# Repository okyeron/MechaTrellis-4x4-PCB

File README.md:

## MechaTrellis RGB Driver PCB for 4x4 Keypad PCB

PCB files for the MechaTrellis 4x4 keypad PCB. Format is Kicad 8.0 schematic and board layout

### Description

MechaTellis is an Adaptation/Remix of the Adafruit NeoTrellis RGB Driver PCB.  

MechaTellis was designed by Steven Noreyko/denki-oto. Original NeoTrellis design by Limor Fried/Ladyada for Adafruit Industries. 

These run the same NeoTrellis seesaw I2C chip and are fully software compatible with the NeoTrellis boards and projects.

A JST-SH 4-pin connector is included that will give you power+data access. Note JST-SH is smaller than the NeoTrellis JST-PH connector.

From the original NeoTrellis 4x4 boards:  

These 4x4 button pad boards are fully tile-able and communicate over I2C. With 5 address pins, you've got the ability to connect up to 32 together in any arrangement you like. [With our trusty seesaw I2C-to-anything chip](https://learn.adafruit.com/adafruit-seesaw-atsamd09-breakout), you don't even need to manage the NeoPixel driving. That's right! Both the button management and LED driving is completely handled for you all over plain I2C. With both Arduino/C++ and CircuitPython/Python library support, you can use these pads with any and all microcontroller or computer boards.

**You can tile up to 32 boards together by soldering them edge-to-edge and soldering closed the I2C address jumpers, then use one I2C connection for all tiled boards!**

### License

Creative Commons Attribution/Share-Alike, all text above must be included in any redistribution. See license.txt for additional details.

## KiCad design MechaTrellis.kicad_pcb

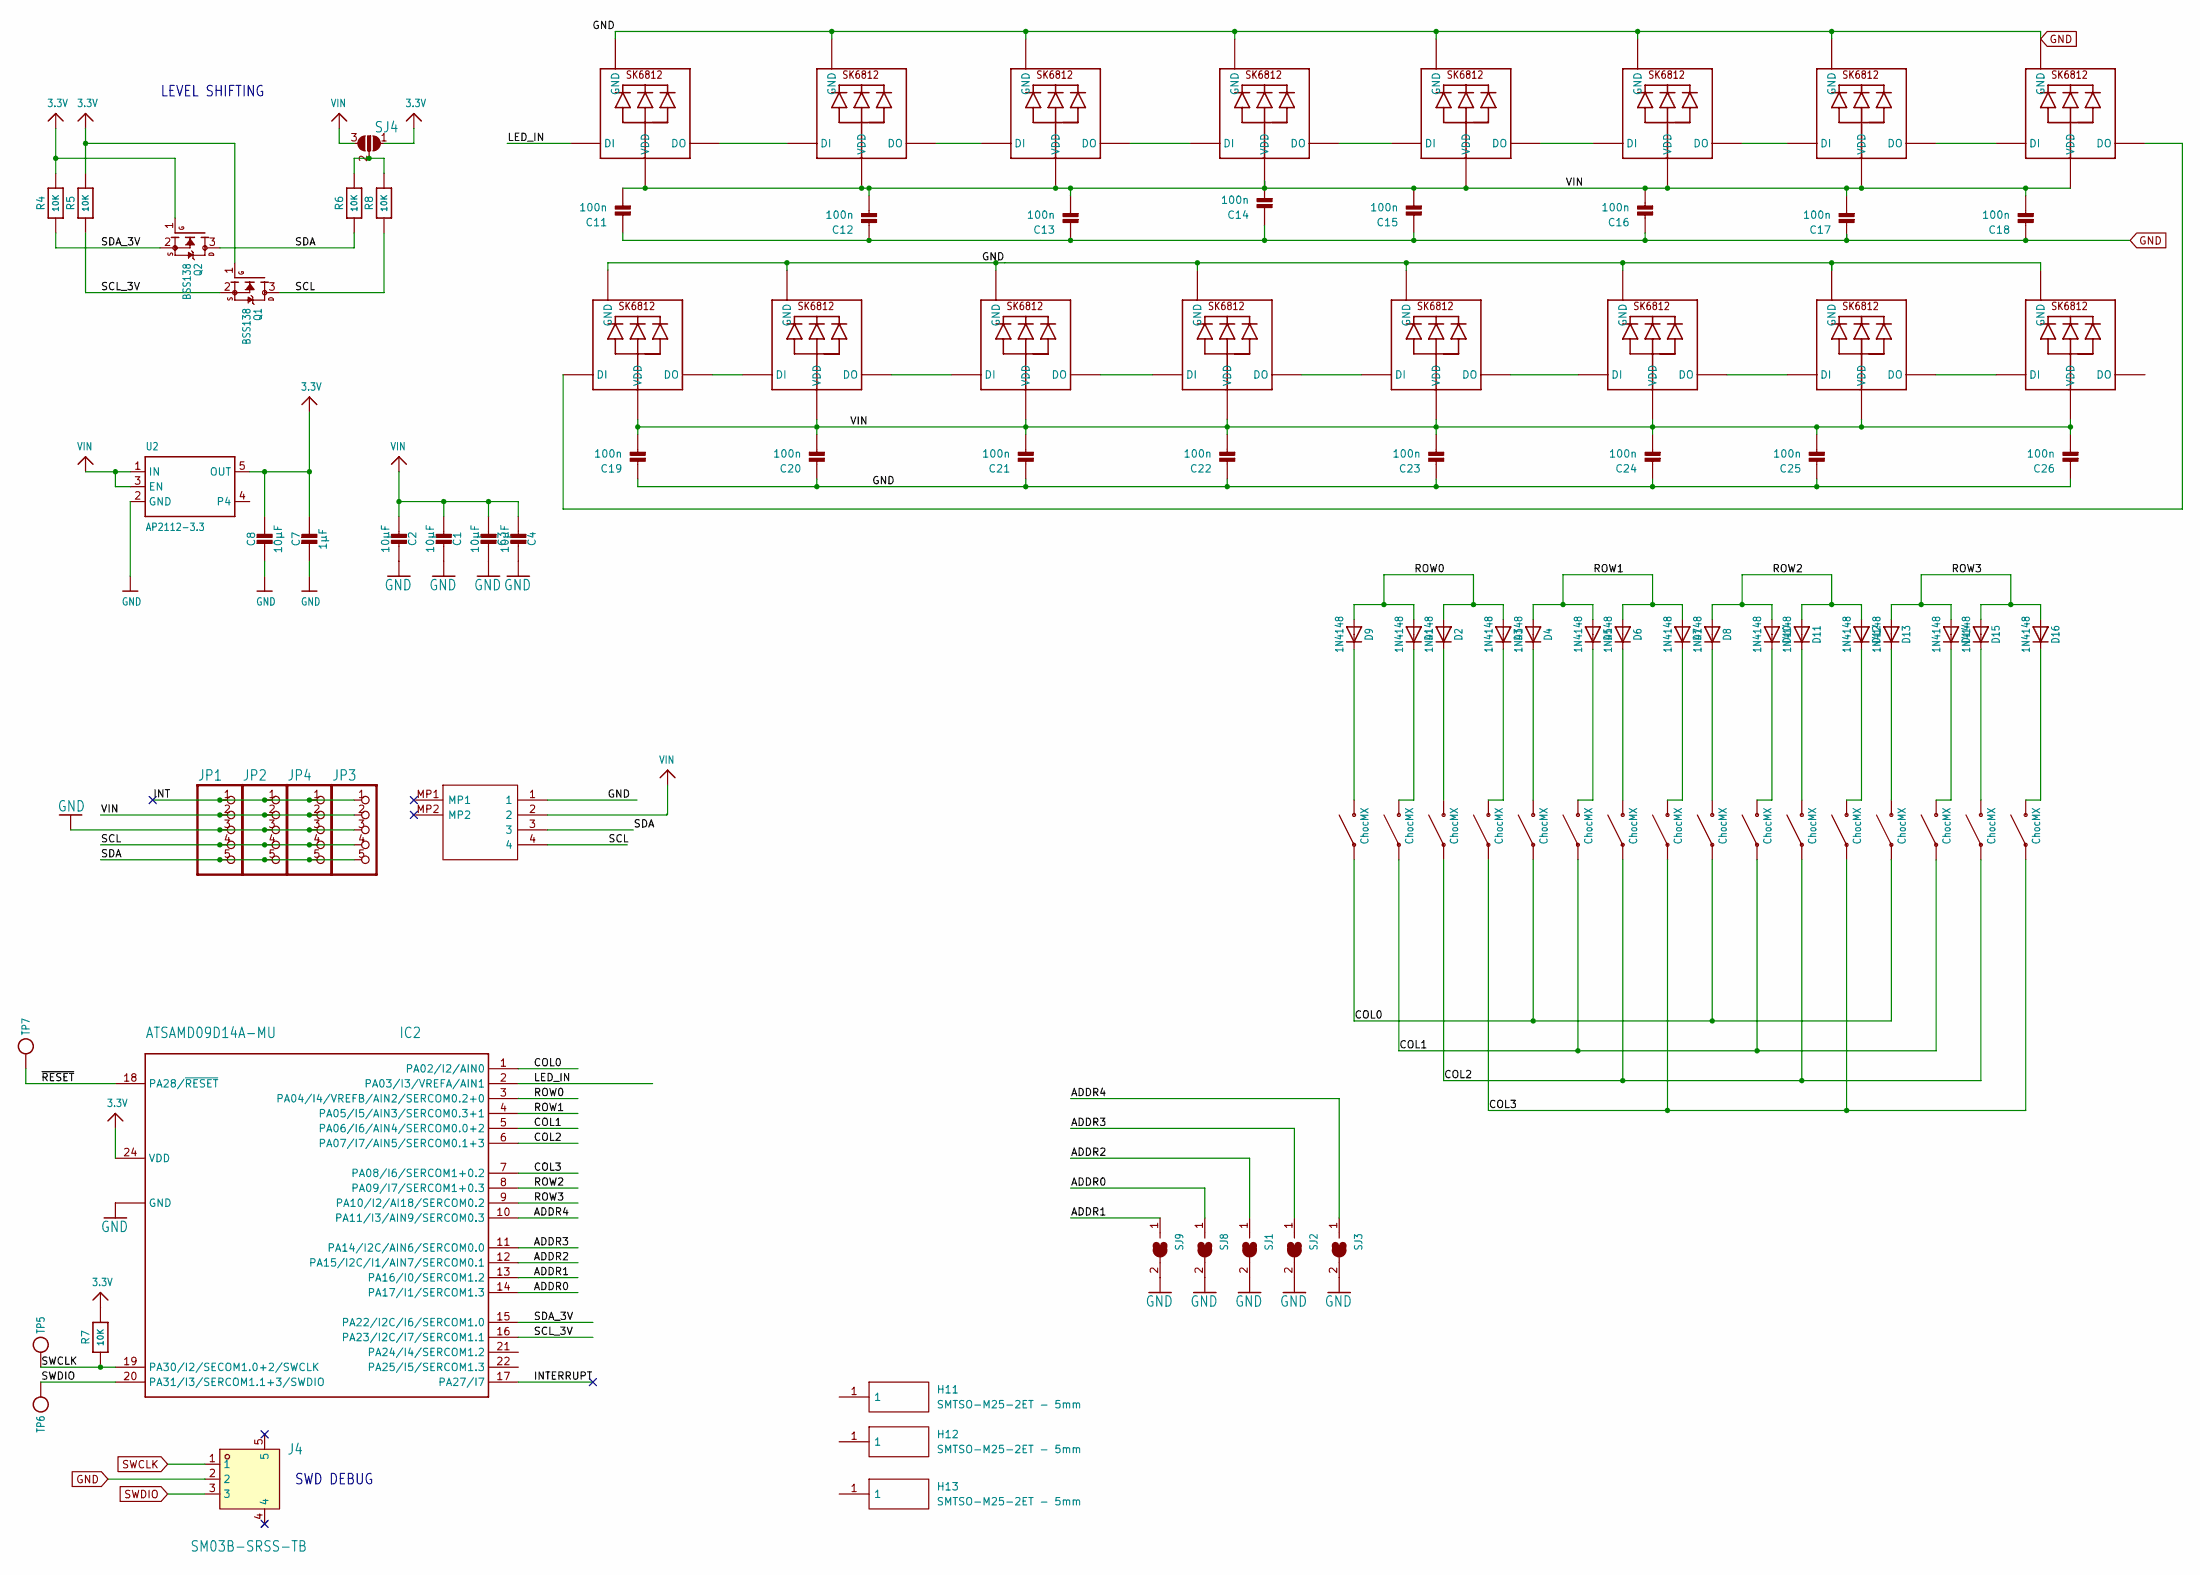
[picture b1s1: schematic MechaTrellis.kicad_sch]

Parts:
C1, C2, C3, C4, C8: 10µF; C_0805_2012Metric
C7: 1µF; C_0603_1608Metric
C11, C12, C13, C14, C15, C16, C17, C18, C19, C20, C21, C22, C23, C24, C25, C26: 100n; C_0603_1608Metric
D1, D2, D3, D4, D5, D6, D7, D8, D9, D10, D11, D12, D13, D14, D15, D16: 1N4148; SOD-323
H11, H12, H13: SMTSO-M25-2ET - 5mm; SMTSOM252ET; Manufacturer_Part_Number SMTSO-M25-2ET; Mouser Part Number 153-SMTSO-M25-2ET
IC2: ATSAMD09D14A-MU; QFN24_4MM
J4: SM03B-SRSS-TB; SM03B-SRSS-TB_LFSN; Manufacturer_Part_Number SM03B-SRSS-TB(LFSN)
JP1, JP2, JP3, JP4: HEADER-1X5EDGESMT; 5P_EDGECONNECT
K01, K02, K03, K04, K05, K06, K07, K08, K09, K10, K11, K12, K13, K14, K15, K16: ChocMX; Choc_MX_combo
LED1, LED2, LED3, LED4, LED5, LED6, LED7, LED8, LED9, LED10, LED11, LED12, LED13, LED14, LED15, LED16: SK6812MINIE; SK6812-MINI-E
Q1, Q2: BSS138; SOT23-R
R4, R5, R6, R7, R8: 10K; R_0603_1608Metric
SJ1, SJ2, SJ3, SJ8, SJ9: SOLDERJUMPER; SolderJumper-2_P1.3mm_Open_TrianglePad1.0x1.5mm
SJ4: SOLDERJUMPER_2WAY; SolderJumper-3_P1.3mm_Open_RoundedPad1.0x1.5mm
TP5, TP6: TESTPOINTROUND2MM; TESTPOINT_ROUND_2MM
TP7: TESTPOINTROUND1.5MM; TESTPOINT_ROUND_1.5MM
U2: AP2112-3.3; SOT23-5@2
X2: STEMMA_I2C_RASMT; SM04BSRSSTB; Manufacturer_Part_Number SM04B-SRSS-TB

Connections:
3.3V: C7.1, C8.1, IC2.24 (VDD), Q1.1 (G), Q2.1 (G), R4.2, R5.2, R7.2, SJ4.1, U2.5 (OUT)
/ADDR0: IC2.14 (PA17/I1/SERCOM1.3), SJ8.1
/ADDR1: IC2.13 (PA16/I0/SERCOM1.2), SJ9.1
/ADDR2: IC2.12 (PA15/I2C/I1/AIN7/SERCOM0.1), SJ1.1
/ADDR3: IC2.11 (PA14/I2C/AIN6/SERCOM0.0), SJ2.1
/ADDR4: IC2.10 (PA11/I3/AIN9/SERCOM0.3), SJ3.1
/COL0: IC2.1 (PA02/I2/AIN0), K01.SW1, K05.SW1, K09.SW1, K13.SW1
/COL1: IC2.5 (PA06/I6/AIN4/SERCOM0.0+2), K02.SW1, K06.SW1, K10.SW1, K14.SW1
/COL2: IC2.6 (PA07/I7/AIN5/SERCOM0.1+3), K03.SW1, K07.SW1, K11.SW1, K15.SW1
/COL3: IC2.7 (PA08/I6/SERCOM1+0.2), K04.SW1, K08.SW1, K12.SW1, K16.SW1
/INT: JP1.1, JP2.1, JP3.1, JP4.1
/INTERRUPT: IC2.17 (PA27/I7)
/LED_IN: IC2.2 (PA03/I3/VREFA/AIN1), LED1.4-DIN (DI)
/ROW0: D1.A, D2.A, D3.A, D9.A, IC2.3 (PA04/I4/VREFB/AIN2/SERCOM0.2+0)
/ROW1: D4.A, D5.A, D6.A, D7.A, IC2.4 (PA05/I5/AIN3/SERCOM0.3+1)
/ROW2: D8.A, D10.A, D11.A, D12.A, IC2.8 (PA09/I7/SERCOM1+0.3)
/ROW3: D13.A, D14.A, D15.A, D16.A, IC2.9 (PA10/I2/AI18/SERCOM0.2)
/SCL: JP1.4, JP2.4, JP3.4, JP4.4, Q1.3 (D), R8.1, X2.4
/SCL_3V: IC2.16 (PA23/I2C/I7/SERCOM1.1), Q1.2 (S), R5.1
/SDA: JP1.5, JP2.5, JP3.5, JP4.5, Q2.3 (D), R6.1, X2.3
/SDA_3V: IC2.15 (PA22/I2C/I6/SERCOM1.0), Q2.2 (S), R4.1
/~RESET: IC2.18 (PA28/~RESET), TP7.P$1
GND: C1.1, C2.1, C3.1, C4.1, C7.2, C8.2, C11.1, C12.1, C13.1, C14.1, C15.1, C16.1, C17.1, C18.1, C19.1, C20.1, C21.1, C22.1, C23.1, C24.1, C25.1, C26.1, IC2.23 (GND), IC2.THERM (GND), JP1.3, JP2.3, JP3.3, JP4.3, LED1.3-GND (GND), LED2.3-GND (GND), LED3.3-GND (GND), LED4.3-GND (GND), LED5.3-GND (GND), LED6.3-GND (GND), LED7.3-GND (GND), LED8.3-GND (GND), LED9.3-GND (GND), LED10.3-GND (GND), LED11.3-GND (GND), LED12.3-GND (GND), LED13.3-GND (GND), LED14.3-GND (GND), LED15.3-GND (GND), LED16.3-GND (GND), SJ1.2, SJ2.2, SJ3.2, SJ8.2, SJ9.2, U2.2 (GND), X2.1; also elsewhere on the board
unnamed: D1.C, K02.SW2
unnamed: D2.C, K03.SW2
unnamed: D3.C, K04.SW2
unnamed: D4.C, K05.SW2
unnamed: D5.C, K06.SW2
unnamed: D6.C, K07.SW2
unnamed: D7.C, K08.SW2
unnamed: D8.C, K09.SW2
unnamed: D9.C, K01.SW2
unnamed: D10.C, K10.SW2
unnamed: D11.C, K11.SW2
unnamed: D12.C, K12.SW2
unnamed: D13.C, K13.SW2
unnamed: D14.C, K14.SW2
unnamed: D15.C, K15.SW2
unnamed: D16.C, K16.SW2
unnamed: LED1.2-OUT (DO), LED2.4-DIN (DI)
unnamed: LED2.2-OUT (DO), LED3.4-DIN (DI)
unnamed: LED3.2-OUT (DO), LED4.4-DIN (DI)
unnamed: LED4.2-OUT (DO), LED5.4-DIN (DI)
unnamed: LED5.2-OUT (DO), LED6.4-DIN (DI)
unnamed: LED6.2-OUT (DO), LED7.4-DIN (DI)
unnamed: LED7.2-OUT (DO), LED8.4-DIN (DI)
unnamed: LED8.2-OUT (DO), LED9.4-DIN (DI)
unnamed: LED9.2-OUT (DO), LED10.4-DIN (DI)
unnamed: LED10.2-OUT (DO), LED11.4-DIN (DI)
unnamed: LED11.2-OUT (DO), LED12.4-DIN (DI)
unnamed: LED12.2-OUT (DO), LED13.4-DIN (DI)
unnamed: LED13.2-OUT (DO), LED14.4-DIN (DI)
unnamed: LED14.2-OUT (DO), LED15.4-DIN (DI)
unnamed: LED15.2-OUT (DO), LED16.4-DIN (DI)
unnamed: R6.2, R8.2, SJ4.2
SWCLK: IC2.19 (PA30/I2/SECOM1.0+2/SWCLK), R7.1, TP5.P$1; also elsewhere on the board
SWDIO: IC2.20 (PA31/I3/SERCOM1.1+3/SWDIO), TP6.P$1; also elsewhere on the board
VIN: C1.2, C2.2, C3.2, C4.2, C11.2, C12.2, C13.2, C14.2, C15.2, C16.2, C17.2, C18.2, C19.2, C20.2, C21.2, C22.2, C23.2, C24.2, C25.2, C26.2, JP1.2, JP2.2, JP3.2, JP4.2, LED1.1-VDD (VDD), LED2.1-VDD (VDD), LED3.1-VDD (VDD), LED4.1-VDD (VDD), LED5.1-VDD (VDD), LED6.1-VDD (VDD), LED7.1-VDD (VDD), LED8.1-VDD (VDD), LED9.1-VDD (VDD), LED10.1-VDD (VDD), LED11.1-VDD (VDD), LED12.1-VDD (VDD), LED13.1-VDD (VDD), LED14.1-VDD (VDD), LED15.1-VDD (VDD), LED16.1-VDD (VDD), SJ4.3, U2.1 (IN), U2.3 (EN), X2.2

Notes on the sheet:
SWD DEBUG
LEVEL SHIFTING

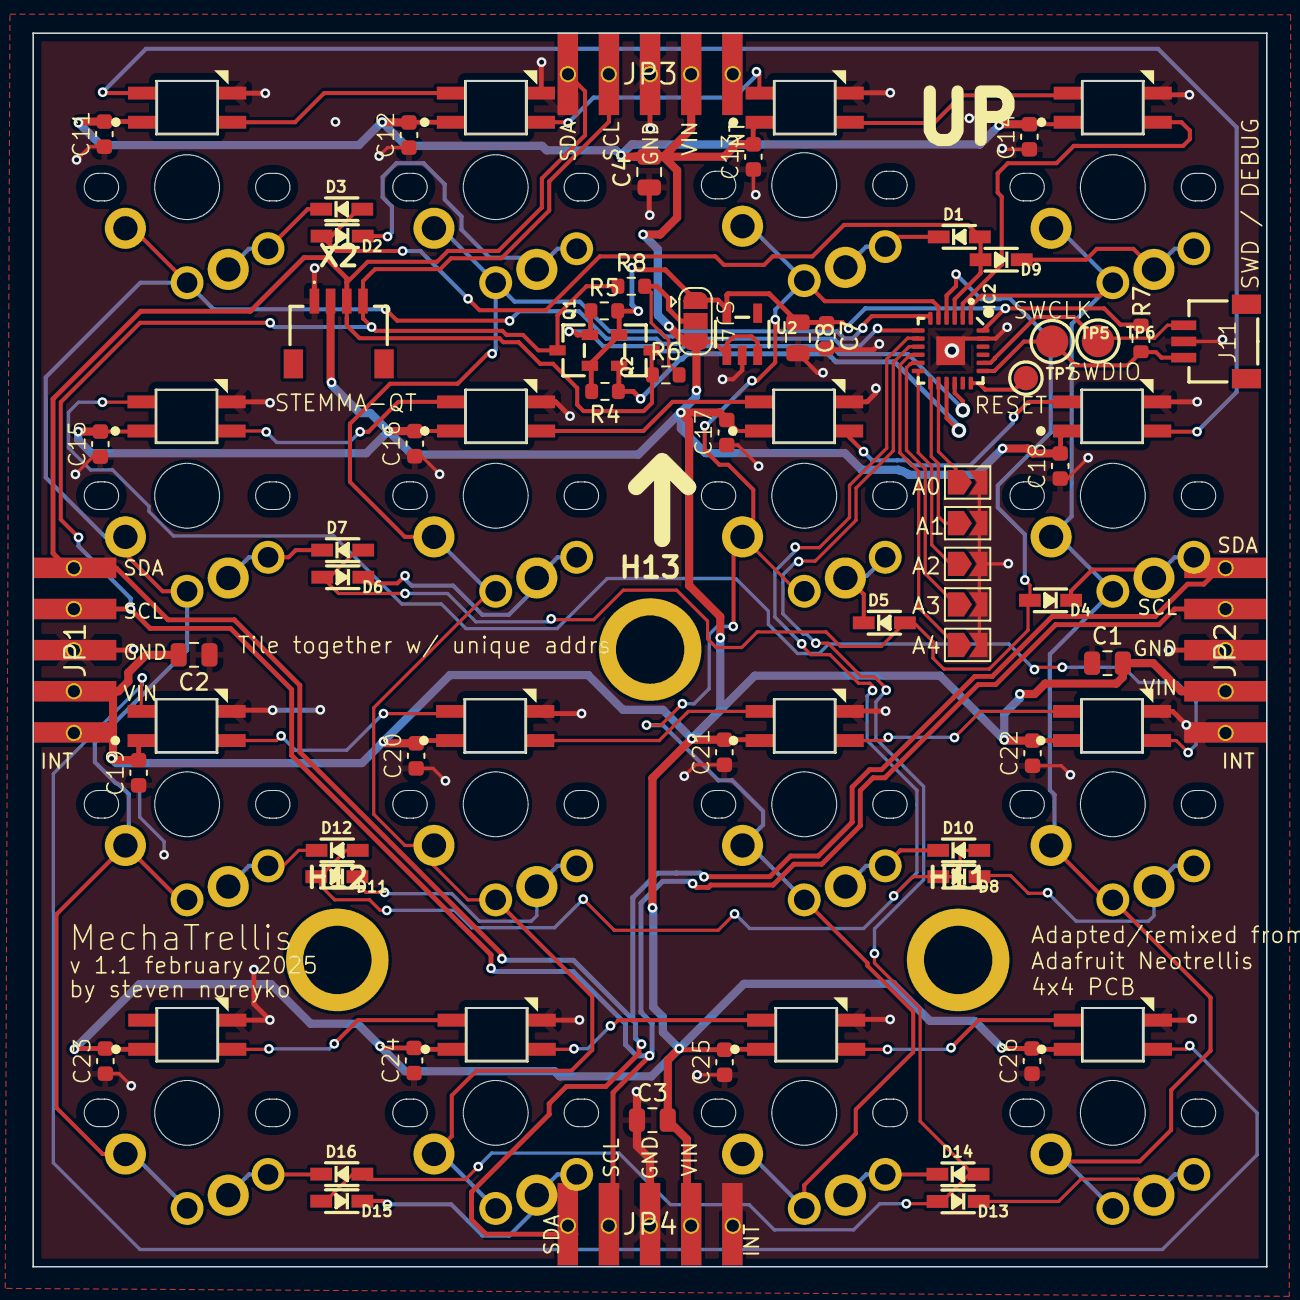
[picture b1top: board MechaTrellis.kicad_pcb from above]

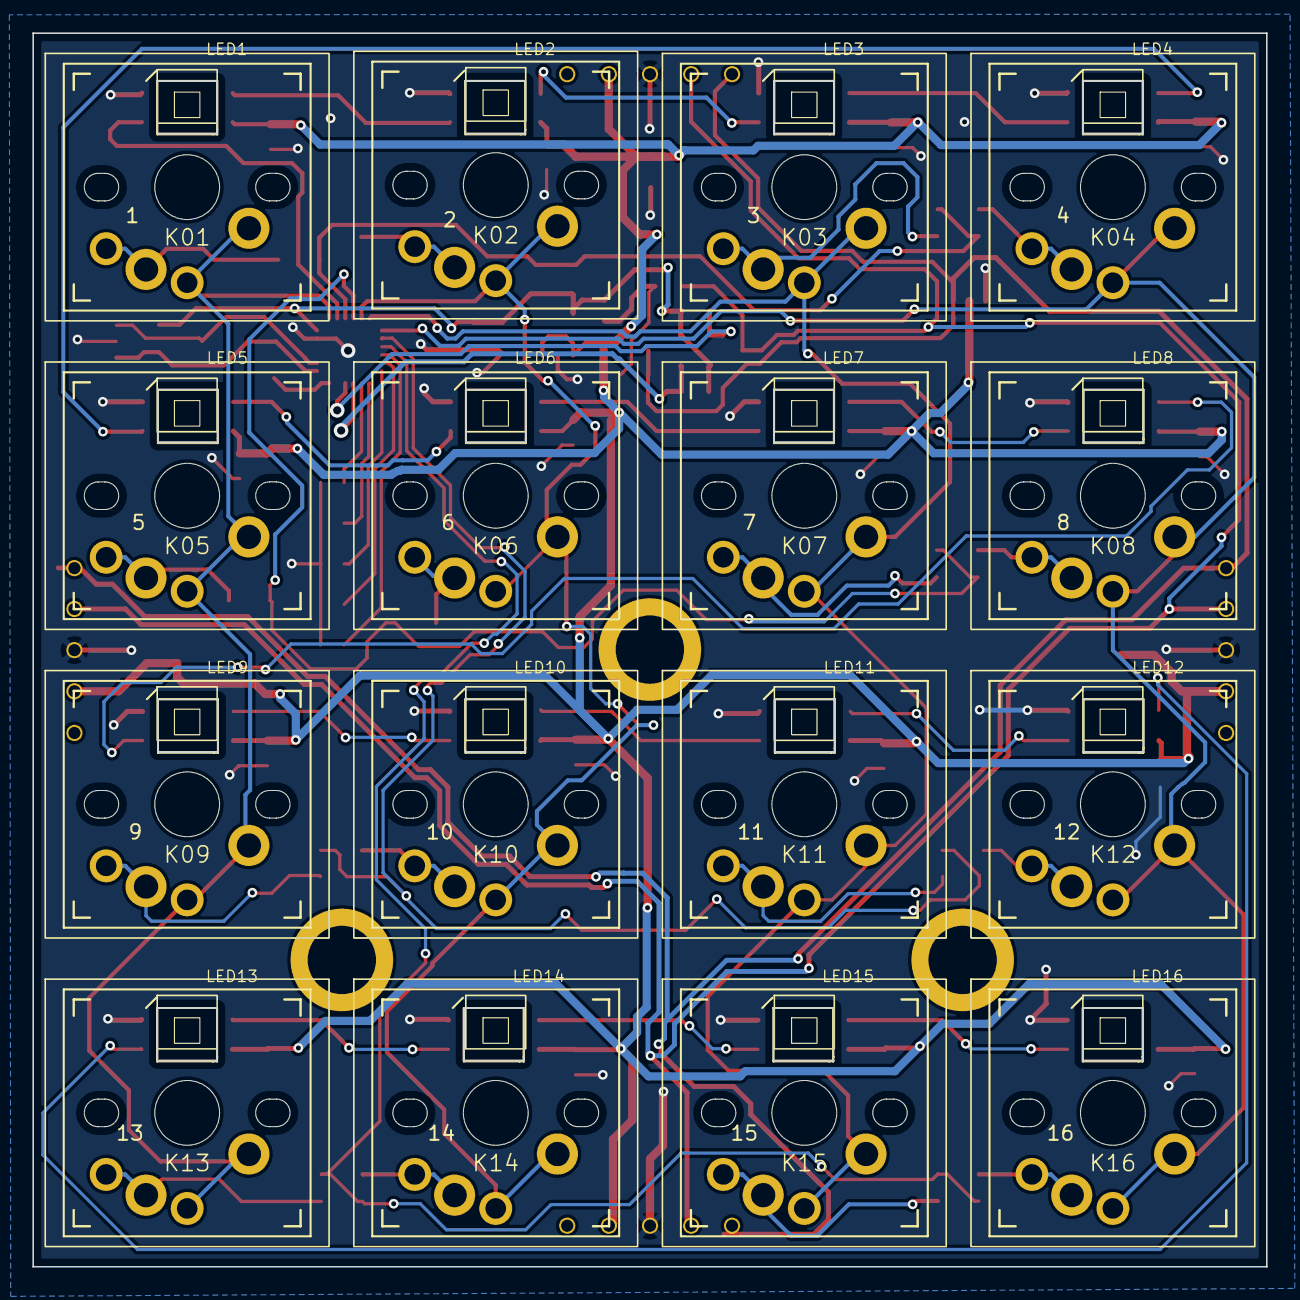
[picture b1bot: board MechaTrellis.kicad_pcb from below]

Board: 2 copper layers, 76.1 x 76.1 mm, 112 parts (32 on the bottom side), 57 nets.

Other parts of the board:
GND: (no value)
GND#2, GND#3: (no value)
J11: SM03B-SRSS-TB; SM03B-SRSS-TB_LFSN
SCL: (no value)
SCL#2, SCL#3, SCL#4: (no value)
SDA: (no value)
SDA#2, SDA#3, SDA#4: (no value)
VIN: (no value)
VIN#2, VIN#3, VIN#4: (no value)

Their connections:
GND: J11.2; also elsewhere on the board
SWCLK: J11.1; also elsewhere on the board
SWDIO: J11.3; also elsewhere on the board

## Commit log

2025-02-20 add files
